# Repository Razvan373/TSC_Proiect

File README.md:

# SmartWatch

Un smartwatch open-source accesibil, construit în jurul microcontrolerului **nRF52840**, cu afișaj **e-paper**, consum redus de energie și conectivitate **Bluetooth Low Energy**.

## Diagramă Bloc

---

## Bill of Materials (BOM)

Tabelul de mai jos conține principalele componente utilizate în proiect, împreună cu capsulele lor, rolul funcțional și link-uri către documentația tehnică unde este disponibilă.

| Componentă | Valoare / Part Number | Pachet | Cant. | Rol | Datasheet |
|-----------|------------------------|--------|-------|-----|-----------|
| NRF52840_QF | nRF52840 | AQFN-73 | 1 | Microcontroler principal cu BLE 5.0 | [Datasheet](https://infocenter.nordicsemi.com/pdf/nRF52840_PS_v1.1.pdf) |
| IC1 | RT6160AWSC | WL-CSP-15 | 1 | Convertor buck-boost DC/DC | [Datasheet](https://www.richtek.com/assets/product_file/RT6160A/DS6160A-05.pdf) |
| IC2 | BMA423 | LGA-12 | 1 | Accelerometru triaxial | [Datasheet](https://www.bosch-sensortec.com/products/motion-sensors/accelerometers/bma423/) |
| IC3 | BQ25180YBGR | DSBGA-8 | 1 | Încărcător pentru baterie LiPo | [Datasheet](https://www.ti.com/lit/ds/symlink/bq25180.pdf) |
| IC4 | DRV2605YZFR | WCSP-9 | 1 | Driver haptic | [Datasheet](https://www.ti.com/lit/ds/symlink/drv2605.pdf) |
| U1 | MAX17048G+T10 | TDFN-8 | 1 | Fuel gauge pentru monitorizarea bateriei | [Datasheet](https://www.analog.com/media/en/technical-documentation/data-sheets/max17048-max17049.pdf) |
| D3 | USBLC6-2SC6Y | SOT-23-6 | 1 | Protecție ESD pentru liniile USB | [Datasheet](https://www.st.com/resource/en/datasheet/usblc6-2.pdf) |
| ANT1 | 2450AT18B100E | SMD | 1 | Antenă chip 2.4GHz | [Datasheet](https://www.johansontechnology.com/datasheets/antennas/2450AT18B100.pdf) |
| X1 | Cristal 32MHz | SMD 2016 | 1 | Sursă principală de ceas | - |
| X2 | Cristal 32.768kHz | SMD 3215 | 1 | Sursă de ceas pentru RTC | - |
| J1 | TC2030-IDC | Tag-Connect | 1 | Interfață SWD pentru programare și debugging | [Datasheet](https://www.tag-connect.com/product/tc2030-idc) |
| J2 | 503480-2400 | FPC-24 | 1 | Conector pentru afișajul e-paper | [Datasheet](https://www.molex.com/en-us/part-list/503480-2400) |
| J4 | KH-TYPE-C-16P | SMD | 1 | Conector USB-C | - |
| Q1 | DMG2305UX-7 | SOT-23 | 1 | MOSFET P-channel pentru circuitul EPD | [Datasheet](https://www.diodes.com/assets/Datasheets/DMG2305UX.pdf) |
| Q3 | SI1308EDL-T1-GE3 | SC-70 | 1 | MOSFET N-channel pentru circuitul EPD | [Datasheet](https://www.vishay.com/docs/68986/si1308edl.pdf) |
| D2, D4, D5 | MBR0530 | SOD-123 | 3 | Diode Schottky pentru etajul EPD | - |
| L1 | 3.9nH | SMD 2012 | 1 | Element din rețeaua RF de adaptare | - |
| L2 | 10µH | SMD 2012 | 1 | Inductor pentru alimentarea nRF | - |
| L3 | 15nH | SMD 2012 | 1 | Filtru RF | - |
| L5 | 68µH | SMD 2012 | 1 | Inductor pentru generatorul EPD | - |
| L7 | FTC252012SR47MBCA | SMD 2012 | 1 | Inductor de putere pentru RT6160 | [JLCPCB](https://jlcpcb.com/partdetail/6763488-FTC252012SR47MBCA/C5832368) |
| SW_UP, SW_DN, SW_ENT | EVP-AKE31A | SMD | 3 | Butoane tactile | - |
| SJ1 | Solder Jumper | SMD | 1 | Jumper de configurare | - |
| R1, R2, R5 | 0Ω | 0201 | 3 | Rezistențe de configurare | - |
| R3, R4 | 3.3kΩ | 0201 | 2 | Pull-up pentru magistrala I2C | - |
| R6, R2_EP_DR, R_PWR_EPD | 10kΩ | 0201 | 3 | Pull-up / pull-down | - |
| R7, R8, R9 | 10kΩ | 0201 | 3 | Pull-down pentru butoane | - |
| R1_USB, R2_USB | 5.1kΩ | 0201 | 2 | Rezistențe CC pentru USB-C | - |
| R_TYPE_SEL | 2.2Ω | 0201 | 1 | Selecție tip display | - |
| R1_EP_DR | 0.47Ω | 0201 | 1 | Limitare / sensing în etajul EPD | - |
| C1, C2, C17, C18 | 12pF | 0201 | 4 | Condensatoare pentru cristale | - |
| C3, C4 | 1pF | 0201 | 2 | Condensatoare pentru adaptare RF | - |
| C9 | 820pF | 0201 | 1 | Condensator de adaptare RF | - |
| C5, C7, C8, C12, C19 | 100nF | 0201 | 5 | Decuplare locală | - |
| C11 | 100pF | 0201 | 1 | Decuplare DEC5 | - |
| C16 | 47nF | 0201 | 1 | Decuplare | - |
| C15 | 1.0µF | 0402 | 1 | Decuplare | - |
| C6, C14, C20, C21, C43, C2-EP-DR | 4.7µF | 0402 | 6 | Condensatoare bulk | - |
| C24, C39, C1-EP-DR | 10µF | 0402 | 3 | Filtrare intrare / ieșire | - |
| C25, C33 | 22µF | 0402 | 2 | Condensatoare ieșire convertor | - |
| C23, C27, C34, C42, EPD_C5 | 0.1µF | 0201 | 5 | Bypass / decuplare | - |
| C29-C32, C37, C38, EPD_C1-C12 | 1µF | 0402 | 15 | Filtrare și stabilizare | - |
| C10, C13, C22 | N.C. | 0201 | 3 | Nepopulate | - |
| Test Pads | - | SMD | 14 | Puncte de test pentru alimentare și debug | - |

---

## Hardware

### Microcontroler principal — nRF52840

Microcontrolerul **nRF52840** reprezintă centrul funcțional al întregului sistem. Acesta asigură procesarea principală, comunicația **Bluetooth Low Energy 5.0**, gestionarea perifericelor și controlul semnalelor digitale necesare funcționării ceasului. Cipul integrează un nucleu **ARM Cortex-M4F** care rulează la **64 MHz**, suficient pentru aplicația vizată, păstrând în același timp un consum redus.

Comunicarea cu restul blocurilor hardware este împărțită astfel:
- **SPI** pentru afișajul e-paper
- **I2C** pentru accelerometru, fuel gauge, încărcător, convertorul DC/DC și driverul haptic
- **GPIO** pentru butoane, semnale de control și linii de întrerupere
- **USB** pentru comunicație și alimentare
- **SWD** pentru programare și depanare

Microcontrolerul este alimentat la **3.3V** din convertorul **RT6160**.

Sursa principală de tact este un cristal de **32 MHz**, conectat la pinii dedicați ai nRF52840. Pentru funcții de timp real și moduri low-power este folosit și un cristal de **32.768 kHz**.

Partea RF este construită în jurul antenei **2450AT18B100E**, conectată la pinul ANT printr-o rețea de adaptare de impedanță formată din **L1, C3, C4 și C9**. Antena a fost poziționată la marginea plăcii, iar în zona de sub aceasta a fost menținut un keepout de cupru pentru a nu afecta performanța radio.

Condensatoarele de decuplare au fost amplasate cât mai aproape de pinii de alimentare, urmând recomandările din designul de referință Nordic.

### Managementul alimentării

#### Încărcător LiPo — BQ25180

Circuitul **BQ25180** se ocupă de încărcarea bateriei LiPo din sursa USB-C. Tensiunea de intrare este preluată de pe linia **VBUS**, iar bateria este conectată pe linia **VBAT**. Acest circuit poate fi configurat prin **I2C**, iar ieșirea sa de întrerupere este conectată la microcontroler pentru semnalizarea evenimentelor de alimentare.

#### Convertor buck-boost — RT6160

Pentru a obține o tensiune stabilă de **3.3V** indiferent de variația tensiunii bateriei, proiectul folosește convertorul **RT6160**. Acesta transformă tensiunea bateriei într-o sursă reglată pentru întreaga logică digitală. Convertorul este conectat la magistrala **I2C**, fiind însoțit de bobina externă și condensatoarele de intrare și ieșire necesare funcționării corecte.

#### Fuel gauge — MAX17048

Circuitul **MAX17048** are rolul de a monitoriza bateria și de a estima starea de încărcare. Acesta comunică prin **I2C**, iar semnalul **ALERT** este dus la un GPIO al microcontrolerului, pentru a permite tratarea rapidă a evenimentelor legate de baterie.

### Afișaj — e-paper 1.54"

Interfața vizuală a ceasului este asigurată de un afișaj **e-paper de 1.54 inch**, cu rezoluție **200 × 200 pixeli**, conectat printr-un conector FPC. Transferul de date se face pe magistrala **SPI**, folosind liniile **MOSI**, **SCK** și **EPD_CS**.

Pe lângă acestea, afișajul mai folosește și semnale GPIO dedicate:
- **EPD_DC**
- **EPD_RST**
- **EPD_BUSY**

Pentru că panoul e-paper are nevoie de tensiuni speciale pentru refresh, a fost introdus un etaj dedicat de generare a tensiunilor, construit cu **Q1**, **Q3**, **D2/D4/D5**, **L5** și mai mulți condensatori. Acest bloc generează liniile **PREVGH** și **PREVGL** necesare funcționării afișajului.

### IMU — BMA423

Pentru detectarea mișcării, proiectul utilizează **BMA423**, un accelerometru triaxial cu consum redus. Acesta este conectat la microcontroler prin **I2C** și oferă două ieșiri de întrerupere, **IMU_INT1** și **IMU_INT2**, utilizabile pentru funcții precum detectarea mișcării, a pașilor sau trezirea sistemului.

### Driver haptic — DRV2605

Feedback-ul tactil este realizat prin circuitul **DRV2605**, care comandă motorul de vibrație. Acesta comunică prin **I2C** și este activat prin semnalul **HAPTIC_EN** controlat de microcontroler.

### USB-C și protecție ESD

Conectorul **USB-C** este folosit atât pentru alimentare, cât și pentru comunicație USB. Liniile de date sunt protejate cu circuitul **USBLC6**, iar pinii **CC** sunt configurați prin rezistențe de **5.1kΩ**, astfel încât portul să fie recunoscut corect în modul device.

### Interfață de debugging — SWD

Programarea și depanarea sunt realizate printr-un conector **Tag-Connect TC2030**, care expune semnalele:
- **SWDIO**
- **SWDCLK**
- **SWO**
- **RESET**
- **3.3V**
- **GND**

Această soluție elimină necesitatea unui header permanent și ajută la păstrarea unui format compact al plăcii.

---

## Mapare pini nRF52840

Tabelul următor prezintă rolul principal al pinilor utilizați pe microcontrolerul nRF52840 în cadrul proiectului.

| Pin | Semnal | Funcție | Interfață |
|-----|--------|---------|-----------|
| P0.00 / XL1 | XL1 | Intrare cristal 32.768kHz | Clock |
| P0.01 / XL2 | XL2 | Ieșire cristal 32.768kHz | Clock |
| P0.04 / AIN2 | IMU_INT1 | Întrerupere 1 de la accelerometru | GPIO |
| P0.05 / AIN3 | IMU_INT2 | Întrerupere 2 de la accelerometru | GPIO |
| P0.06 | EPD_CS | Chip Select pentru e-paper | SPI |
| P0.07 | EPD_DC | Selectare date / comandă display | GPIO |
| P0.08 | EPD_RST | Reset pentru display | GPIO |
| P0.09 / NFC1 | PMIC_INT | Întrerupere de la BQ25180 | GPIO |
| P0.11 | SCK | Clock SPI pentru e-paper | SPI |
| P0.12 | MOSI | Linie date SPI pentru e-paper | SPI |
| P0.13 | EPD_BUSY | Semnal busy de la display | GPIO |
| P0.14 | SCL | Clock magistrală I2C | I2C |
| P0.15 | SDA | Linie date magistrală I2C | I2C |
| P0.18 / RESET | RESET | Reset sistem | Reset |
| P0.19 | HAPTIC_EN | Enable pentru driverul haptic | GPIO |
| P0.26 | SW_UP | Buton sus | GPIO |
| P0.27 | SW_DN | Buton jos | GPIO |
| P1.00 | SW_ENT | Buton enter / select | GPIO |
| P1.01 | ALERT | Alertă de la MAX17048 | GPIO |
| P1.09 | SWO | Debug trace output | Debug |
| XC1 / XC2 | Crystal | Cristal 32MHz | Clock |
| ANT | RF | Antenă prin rețea de adaptare | RF |
| VBUS | USB_VBUS | Alimentare USB 5V | Power |
| D+ / D- | USB Data | Linii de date USB | USB |
| SWDIO | Debug | Linie date SWD | Debug |
| SWDCLK | Debug | Linie clock SWD | Debug |

**Magistrala I2C** este comună pentru:
- **BMA423**
- **BQ25180**
- **RT6160**
- **DRV2605**
- **MAX17048**

Liniile **SDA** și **SCL** sunt trase la **3.3V** prin rezistențele **R3** și **R4**.

---

## Detalii design PCB

### Specificații generale

- **Dimensiuni placă:** 46 mm × 35 mm
- **Formă:** colțuri rotunjite
- **Număr de straturi:** 2
- **Straturi folosite:** Top și Bottom
- **Grosime PCB:** 1.0 mm
- **Lățime trasee semnal:** 0.15 mm
- **Lățime trasee putere:** 0.3 mm
- **Montaj componente:** exclusiv pe stratul Top

### Organizarea straturilor

Placa a fost proiectată pe **două straturi**, iar ambele straturi includ și **zone de plan de masă (GND pour)** pentru a îmbunătăți returul de curent, stabilitatea electrică și comportamentul EMI.

| Strat | Rol principal |
|-------|---------------|
| Top | rutare semnale, plasare componente, plan GND |
| Bottom | rutare suplimentară și plan GND |

### Decizii de proiectare și erori acceptate

În timpul proiectării au existat anumite avertismente DRC care au fost analizate manual și acceptate, deoarece rezultau din constrângeri reale de spațiu sau din cerințe mecanice.

#### Erori de lățime traseu

Pentru liniile de putere precum **3V3**, **VBAT**, **VBUS** sau alte rețele similare, regula de proiectare impunea o lățime de **0.3 mm**. În anumite zone foarte aglomerate ale plăcii, mai ales în apropierea capsulelor fine și a grupurilor dense de componente pasive, această lățime nu a putut fi păstrată pe întreaga lungime, astfel că unele segmente scurte au fost rutate mai îngust. Aceste cazuri au fost acceptate.

#### Erori de clearance

În unele regiuni compacte, în special în jurul microcontrolerului și în zonele cu densitate mare de trasee, anumite segmente de cupru au ajuns mai aproape decât clearance-ul ideal. Aceste situații au fost verificate manual și nu au indicat existența unor scurtcircuite reale.

#### Avertismente legate de planele GND

Fiindcă atât pe Top, cât și pe Bottom au fost folosite planuri de masă, anumite mesaje de clearance sau suprapunere au apărut între zone care aparțin aceleiași rețele **GND**. Aceste avertismente nu afectează funcționarea electrică a plăcii.

#### Extindere peste conturul plăcii

Butoanele tactile și conectorul USB-C sunt poziționate astfel încât să iasă parțial în afara conturului PCB-ului. Acest lucru a fost făcut intenționat pentru alinierea cu decupajele carcasei.

#### Componente nepopulate

Anumite condensatoare marcate **N.C.** sau **DNP** au rămas în schemă și layout pentru compatibilitate cu designul de referință, dar nu sunt montate în varianta finală.

#### Vias de masă și continuitate GND

Au fost adăugate mai multe căi de masă distribuite pe placă pentru a îmbunătăți continuitatea între planele GND și pentru a oferi trasee de retur mai bune, mai ales în jurul zonei RF și a microcontrolerului.

---

## Design PCB

Layout-ul plăcii a fost realizat cu accent pe compactitate, integrare mecanică și păstrarea unor rute cât mai clare între blocurile funcționale. Toate componentele au fost montate pe stratul **Top**, ceea ce simplifică asamblarea și reduce complexitatea mecanică.

Microcontrolerul a fost poziționat central pentru a facilita distribuția semnalelor către afișaj, senzori, partea de alimentare și interfața de debugging. Blocurile de alimentare au fost păstrate relativ aproape unele de altele pentru a minimiza lungimea traseelor de putere, iar zona RF a fost plasată la marginea plăcii pentru a permite funcționarea corectă a antenei.

În realizarea layout-ului au fost urmărite următoarele principii:
- trasee scurte pentru alimentare și decuplare
- gruparea componentelor pe funcții
- separarea cât mai clară a zonei RF de restul circuitului
- acces mecanic bun pentru USB-C și butoane
- folosirea planurilor GND pe ambele straturi pentru integritate electrică mai bună

Imaginile cu stratul superior și cel inferior sunt incluse în secțiunea de imagini a repository-ului pentru a evidenția modul de rutare și distribuția componentelor.
| Top Layer | Bottom Layer |
|:---:|:---:|
|  |  |

---

## Design schematic

Schema electrică a fost organizată modular, astfel încât fiecare subsistem important să poată fi urmărit separat și ușor de înțeles. Proiectul include blocuri distincte pentru:
- microcontroler și tact
- alimentare și încărcare baterie
- monitorizare baterie
- afișaj e-paper și etajul său de comandă
- accelerometru
- driver haptic
- interfață USB
- interfață SWD

Această structurare ajută atât în faza de proiectare, cât și în etapa de verificare și review. Conexiunile dintre blocuri sunt realizate coerent, iar magistralele principale, cum ar fi **I2C** și **SPI**, sunt evidențiate clar în schemă.

De asemenea, schema conține și componente auxiliare importante:
- rezistențe de pull-up și pull-down
- condensatoare de decuplare și filtrare
- elemente de adaptare RF
- conectori și puncte de test

Capturile de ecran ale schemei sunt incluse în repository pentru a susține documentația hardware.

---

## Structura repository-ului

Structura proiectului este organizată astfel încât fișierele de proiectare, fabricație, randare și documentare să fie ușor de identificat.

```text
├── Hardware/
│   ├── InkTime_Schematic.sch
│   └── InkTime_Board.brd
├── Manufacturing/
│   ├── gerbers.zip
│   ├── InkTime_BOM.bom
│   └── InkTime_PnP.cpl
├── Mechanical/
│   ├── InkTime_step.step
│   └── InkTime_complete.f3z
├── Images/
│   ├── 2D_PCB/
│   ├── 3D_PCB/
│   ├── InkTime/
│   └── Schematic/
├── LICENSE
└── README.md

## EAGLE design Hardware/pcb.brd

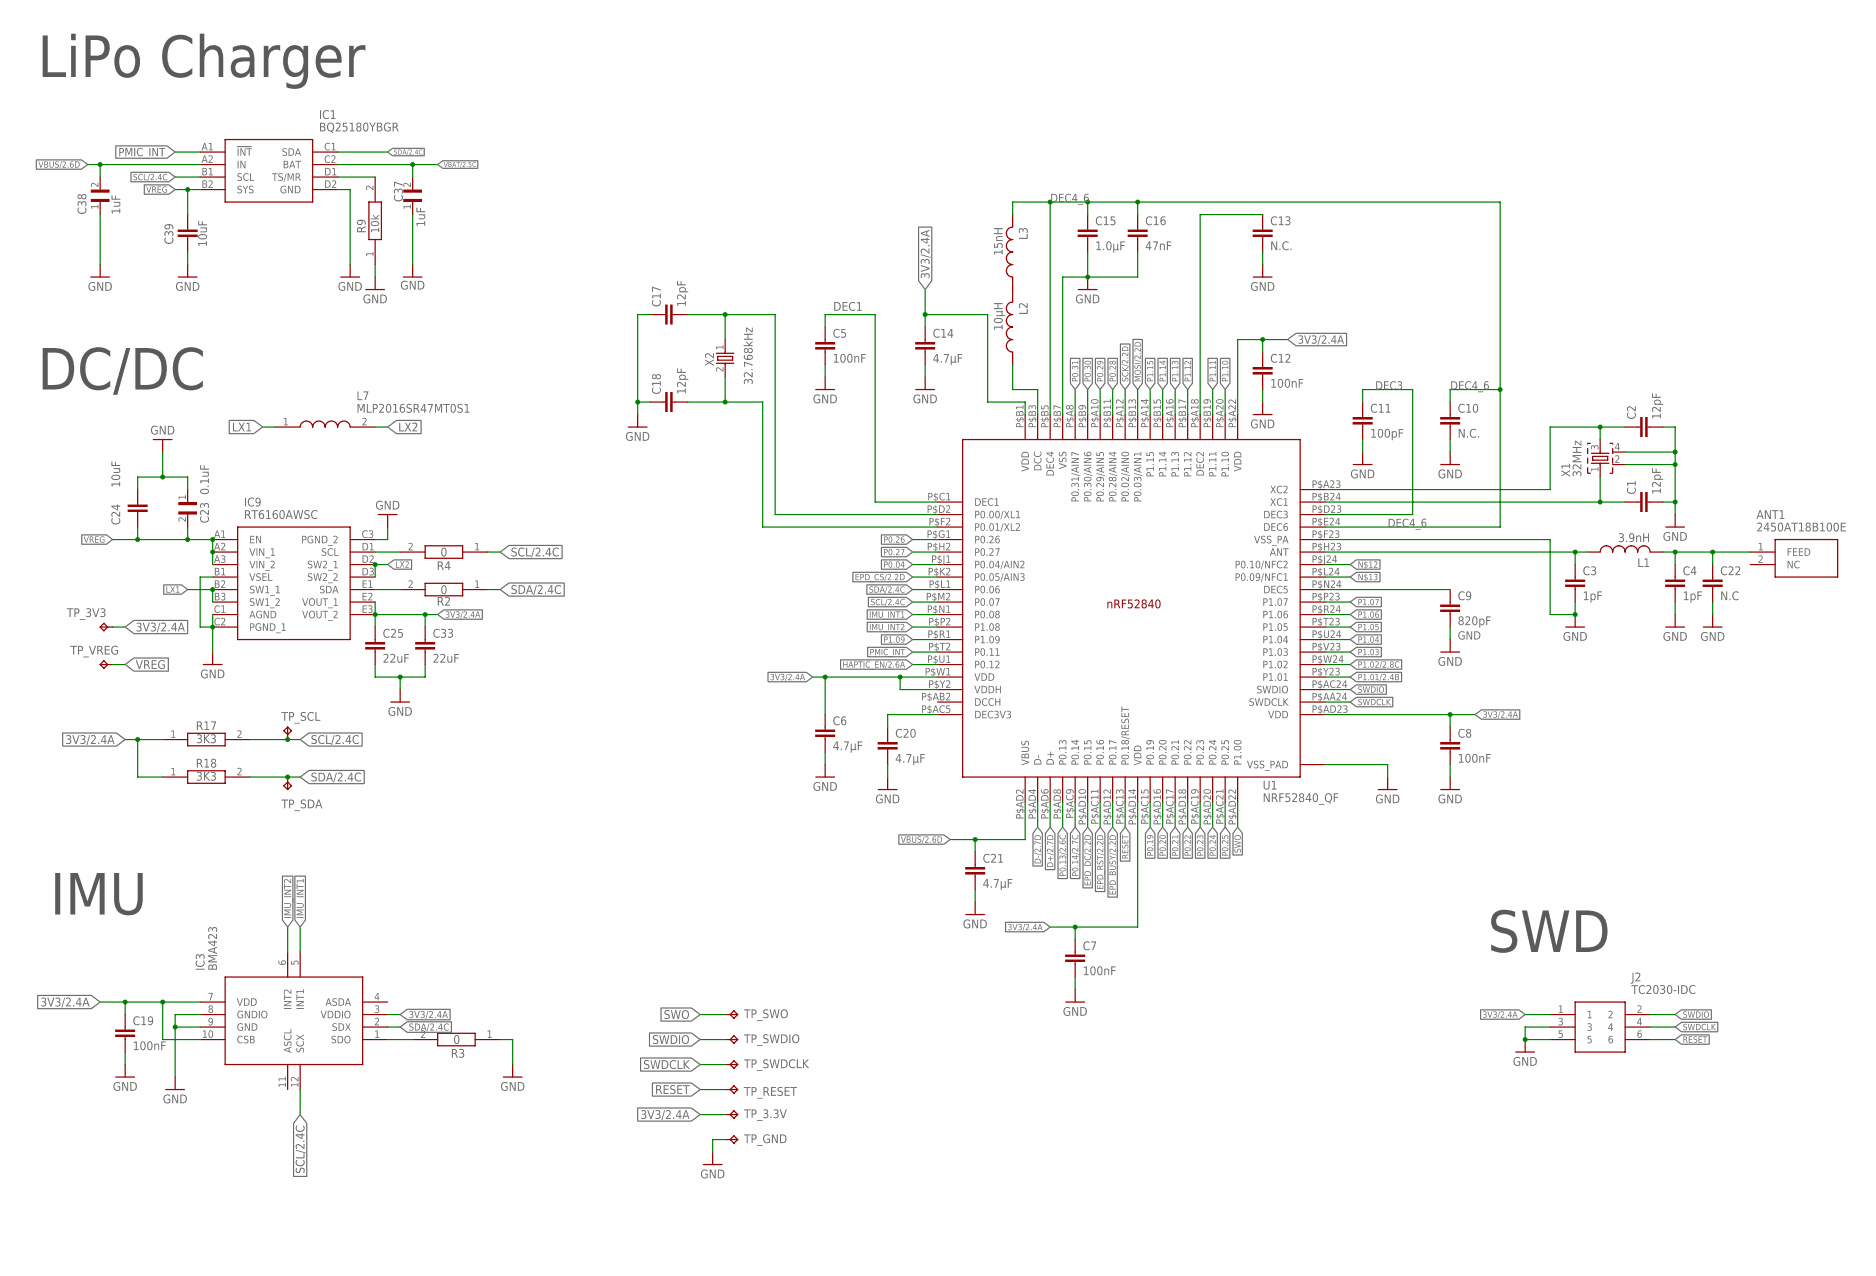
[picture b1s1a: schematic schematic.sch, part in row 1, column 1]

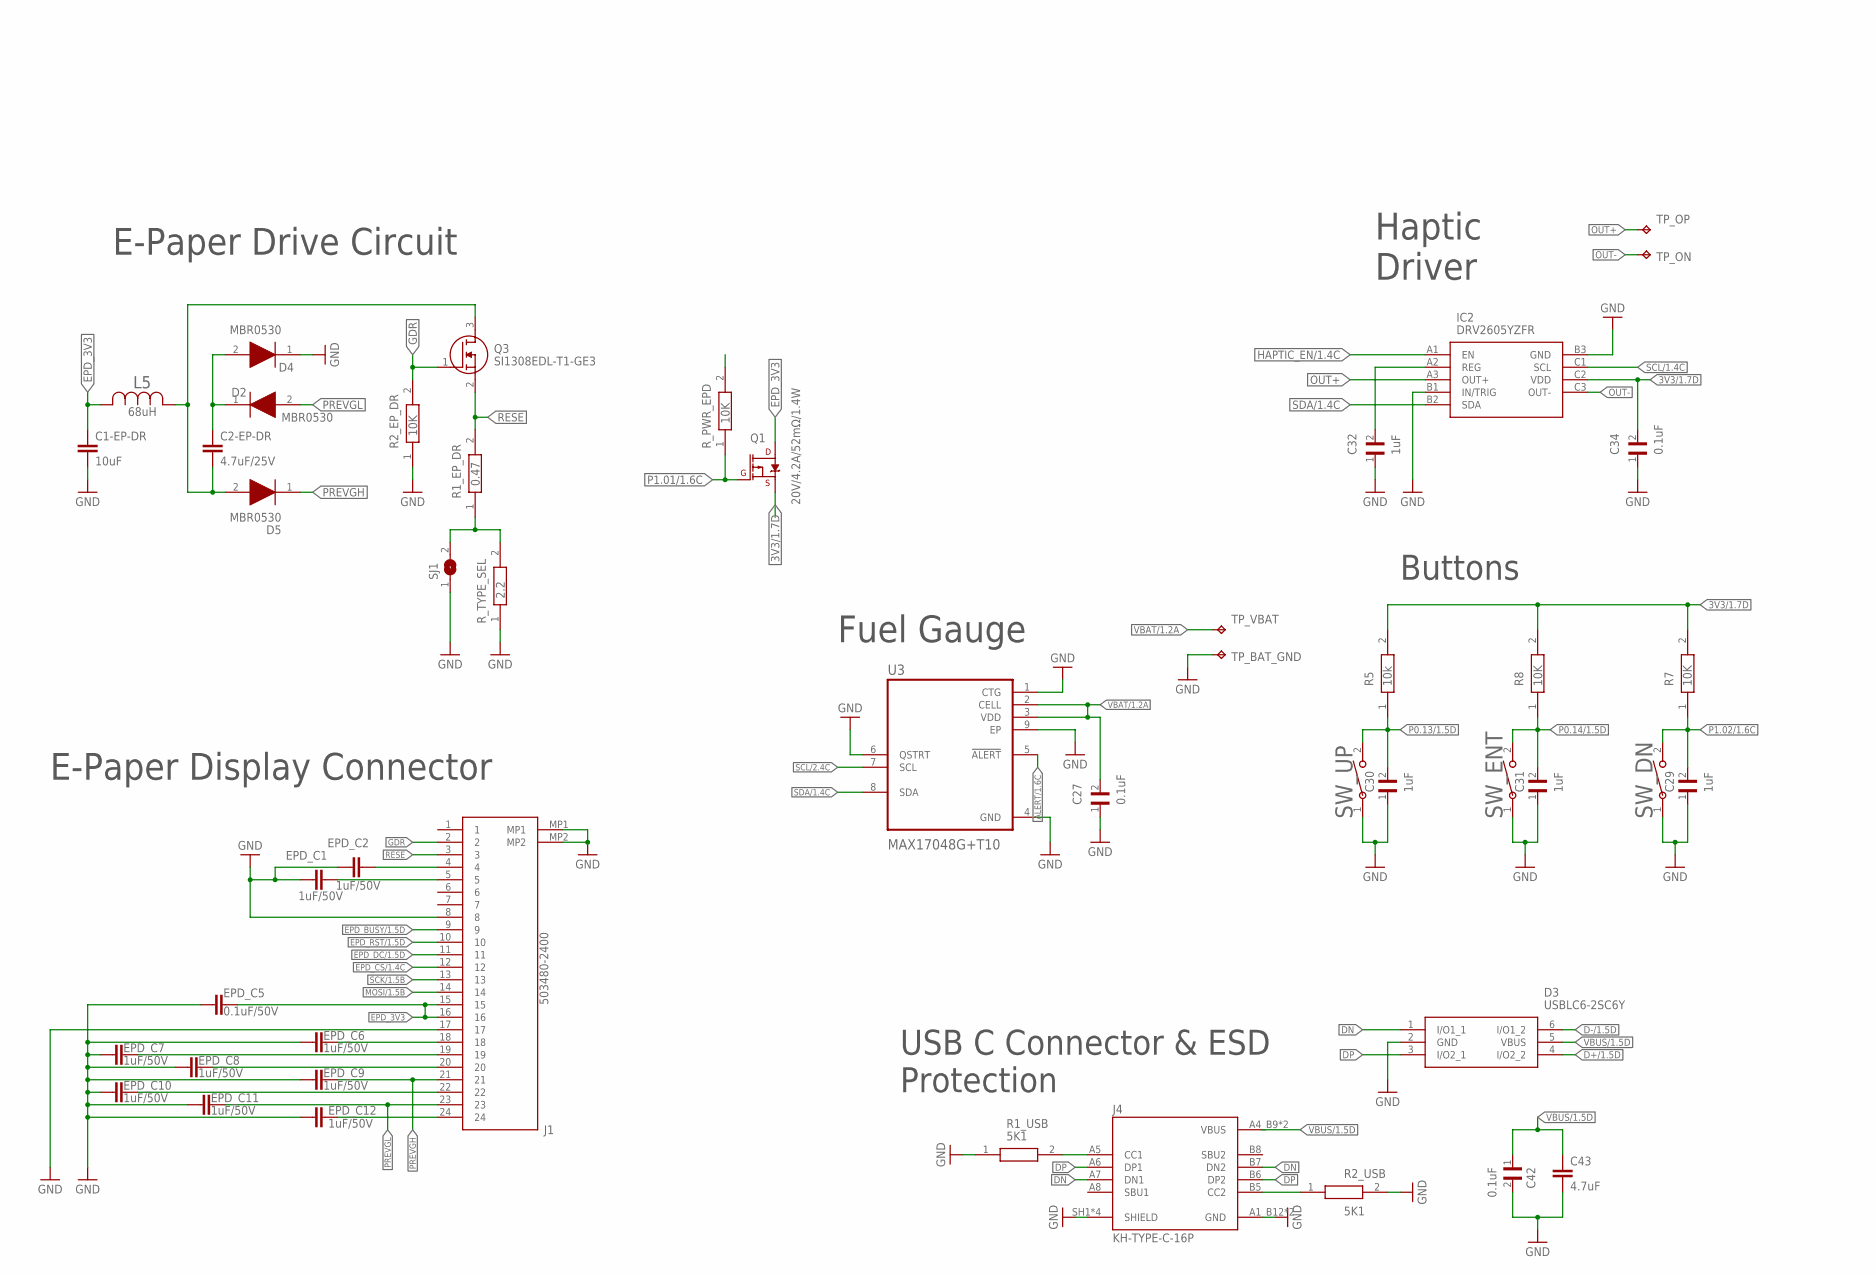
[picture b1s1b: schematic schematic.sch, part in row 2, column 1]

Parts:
ANT1: 2450AT18B100E; 2450AT18B100E_ANTC3216X140N
C1, C2, C17, C18: 12pF; NORDIC_NRF_3_RESC0201_L
C1-EP-DR, C24, C39: 10uF; PERFECT_0402_0402
C2-EP-DR: 4.7uF/25V; PERFECT_0402_0402
C3, C4: 1pF; NORDIC_NRF_3_RESC0201_L
C5, C7, C8, C12, C19: 100nF; NORDIC_NRF_3_RESC0201_L
C6, C14, C20, C21: 4.7µF; PERFECT_0402_0402
C9: 820pF; NORDIC_NRF_3_RESC0201_L
C10, C13: N.C.; NORDIC_NRF_3_RESC0201_L
C11: 100pF; NORDIC_NRF_3_RESC0201_L
C15: 1.0µF; PERFECT_0402_0402
C16: 47nF; NORDIC_NRF_3_RESC0201_L
C22: N.C; NORDIC_NRF_3_RESC0201_L
C23, C27, C34, C42: 0.1uF; ERA-1AEB3401C_0201
C25, C33: 22uF; PERFECT_0402_0402
C29, C30, C31, C32, C37, C38: 1uF; ERA-1AEB3401C_0201
C43: 4.7uF; PERFECT_0402_0402
D2, D4, D5: MBR0530; ESP32_C6_LIBRARY_5_SOD3716X135N
D3: USBLC6-2SC6Y; ESP32_C6_LIBRARY_3_SOT95P280X145-6N
EPD_C1, EPD_C2, EPD_C6, EPD_C7, EPD_C8, EPD_C9, EPD_C10, EPD_C11, EPD_C12: 1uF/50V; PERFECT_0402_0402
EPD_C5: 0.1uF/50V; NORDIC_NRF_3_RESC0201_L
IC1: BQ25180YBGR; BQ25180YBGR_BGA8C40P2X4_100X155X50
IC2: DRV2605YZFR; DRV2605YZFR_BGA9C50P3X3_144X144X62
IC3: BMA423; BMA423_BMA423
IC9: RT6160AWSC; RT6160AWSC_BGA15C40P3X5_140X230X60
J1: 503480-2400; 503480-2400_5034802400
J2: TC2030-IDC; TC2030-IDC_TC2030IDC
J4: KH-TYPE-C-16P; KH-TYPE-C-16P_KINGHELM_KH-TYPE-C-16P
L1: 3.9nH; NORDIC_NRF_2_RESC0402_N
L2: 10µH; NORDIC_NRF_2_RESC0402_N
L3: 15nH; NORDIC_NRF_2_RESC0402_N
L5: 68uH; ESP32_C6_LIBRARY_2_IND_4828-WE-TPC_WRE
L7: MLP2016SR47MT0S1; MLP2016SR47MT0S1_INDC2016X100N
Q1: 20V/4.2A/52mΩ/1.4W; ESP32_C6_LIBRARY_4_ESP32_C6_LIBRARY_4_ESP32_C6_LIBRARY_4_ES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
Q3: SI1308EDL-T1-GE3; ESP32_C6_LIBRARY_6_SOT65P210X110-3N
R1_EP_DR: 0.47; CPF0201D7K68C1_0201
R1_USB, R2_USB: 5K1; CPF0201D7K68C1_0201
R2, R4: 0; ERA-1AEB3401C_0201
R2_EP_DR, R7, R8: 10K; CPF0201D7K68C1_0201
R3: 0; CPF0201D7K68C1_0201
R5: 10k; CPF0201D7K68C1_0201
R9: 10k; ERA-1AEB3401C_0201
R17, R18: 3K3; ERA-1AEB3401C_0201
R_PWR_EPD: 10K; CPF0201D7K68C1_0201
R_TYPE_SEL: 2.2; CPF0201D7K68C1_0201
SJ1: ESP32_C6_LIBRARY_7_JUMPER_SJ
SW_DN: 2025-10-22_07-23-44_LIBRARY_EVP-AKE31ASW_EVP-AKE3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; 2025-10-22_07-23-44_LIBRARY_SW_EVP-AKE31A_PAN
SW_ENT: 2025-10-22_07-23-44_LIBRARY_EVP-AKE31ASW_EVP-AKE3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; 2025-10-22_07-23-44_LIBRARY_SW_EVP-AKE31A_PAN
SW_UP: 2025-10-22_07-23-44_LIBRARY_EVP-AKE31ASW_EVP-AKE3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; 2025-10-22_07-23-44_LIBRARY_SW_EVP-AKE31A_PAN
TP_3.3V, TP_3V3: HECTOR_WATCH_1_TPTP20R; HECTOR_WATCH_1_TP20R
TP_BAT_GND: HECTOR_WATCH_1_TPTP20R; HECTOR_WATCH_1_TP20R
TP_GND: HECTOR_WATCH_1_TPTP20R; HECTOR_WATCH_1_TP20R
TP_ON: HECTOR_WATCH_1_TPTP20R; HECTOR_WATCH_1_TP20R
TP_OP: HECTOR_WATCH_1_TPTP20R; HECTOR_WATCH_1_TP20R
TP_RESET: HECTOR_WATCH_1_TPTP20R; HECTOR_WATCH_1_TP20R
TP_SCL: HECTOR_WATCH_1_TPTP20R; HECTOR_WATCH_1_TP20R
TP_SDA: HECTOR_WATCH_1_TPTP20R; HECTOR_WATCH_1_TP20R
TP_SWDCLK: HECTOR_WATCH_1_TPTP20R; HECTOR_WATCH_1_TP20R
TP_SWDIO: HECTOR_WATCH_1_TPTP20R; HECTOR_WATCH_1_TP20R
TP_SWO: HECTOR_WATCH_1_TPTP20R; HECTOR_WATCH_1_TP20R
TP_VBAT: HECTOR_WATCH_1_TPTP20R; HECTOR_WATCH_1_TP20R
TP_VREG: HECTOR_WATCH_1_TPTP20R; HECTOR_WATCH_1_TP20R
U1: NRF52840_QF; NORDIC_NRF_4_AQFN50P700X700X85_HS-74N
U3: MAX17048G+T10; ESP32_C6_LIBRARY_SON50P200X200X80-9N
X1: 32MHz; NORDIC_NRF_BT-XTAL_2016_N
X2: 32.768kHz; NORDIC_NRF_1_XTAL_3215_N

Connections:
3V3/1.7D: C34.2, IC2.C2 (VDD), Q1.2 (S), R5.2, R7.2, R8.2
3V3/2.4A: C6.1, C7.1, C8.1, C12.1, C14.1, C19.1, C25.1, C33.1, IC3.3 (VDDIO), IC3.7 (VDD), IC3.10 (CSB), IC9.E2 (VOUT_1), IC9.E3 (VOUT_2), J2.1, R17.1, R18.1, TP_3.3V.TP, TP_3V3.TP, U1.P$A22 (VDD), U1.P$AD14 (VDD), U1.P$AD23 (VDD), U1.P$B1 (VDD), U1.P$W1 (VDD), U1.P$Y2 (VDDH)
ALERT/1.6C: U3.5 (!ALERT)
D+/1.5D: D3.4 (I/O2_2)
D+/2.7D: U1.P$AD6 (D+)
D-/1.5D: D3.6 (I/O1_2)
D-/2.7D: U1.P$AD4 (D-)
DEC1: C5.1, U1.P$C1 (DEC1)
DEC3: C11.1, U1.P$D23 (DEC3)
DEC4_6: C10.1, C15.1, C16.1, L3.2, U1.P$B5 (DEC4), U1.P$E24 (DEC6)
DN: D3.1 (I/O1_1), J4.A7 (DN1), J4.B7 (DN2)
DP: D3.3 (I/O2_1), J4.A6 (DP1), J4.B6 (DP2)
EPD_3V3: C1-EP-DR.1, EPD_C5.2, J1.15, J1.16, L5.2, Q1.3 (D)
EPD_BUSY/1.5D: J1.9
EPD_BUSY/2.2D: U1.P$AD12 (P0.17)
EPD_CS/1.4C: J1.12
EPD_CS/2.2D: U1.P$K2 (P0.05/AIN3)
EPD_DC/1.5D: J1.11
EPD_DC/2.2D: U1.P$AD10 (P0.15)
EPD_RST/1.5D: J1.10
EPD_RST/2.2D: U1.P$AC11 (P0.16)
GDR: J1.2, Q3.1 (G), R2_EP_DR.2
GND: C1.2, C1-EP-DR.2, C2.2, C3.2, C4.2, C5.2, C6.2, C7.2, C8.2, C9.2, C10.2, C11.2, C12.2, C13.2, C14.2, C15.2, C16.2, C17.1, C18.1, C19.2, C20.2, C21.2, C22.2, C23.1, C24.1, C25.2, C27.1, C29.1, C30.1, C31.1, C32.1, C33.2, C34.1, C37.1, C38.1, C39.2, C42.2, C43.2, D3.2 (GND), D4.1 (K), EPD_C1.1, EPD_C2.1, EPD_C5.1, EPD_C6.1, EPD_C7.1, EPD_C8.1, EPD_C9.1, EPD_C10.1, EPD_C11.1, EPD_C12.1, IC1.D2 (GND), IC2.B1 (IN/TRIG), IC2.B3 (GND), IC3.8 (GNDIO), IC3.9 (GND), IC9.B1 (VSEL), IC9.C1 (AGND), IC9.C2 (PGND_1), IC9.C3 (PGND_2), J1.8, J1.17, J1.MP1, J1.MP2, J2.3, J2.5, J4.A1_B12 (GND), J4.A12_B1 (GND), J4.SH1 (SHIELD), J4.SH2 (SHIELD), J4.SH3 (SHIELD), J4.SH4 (SHIELD), R1_USB.1, R2_EP_DR.1, R2_USB.2, R3.1, R9.1, R_TYPE_SEL.1, SJ1.1, SW_DN.1, SW_ENT.1, SW_UP.1, TP_BAT_GND.TP, TP_GND.TP, U1.P$74 (VSS_PAD), U1.P$75 (VSS_PAD), U1.P$76 (VSS_PAD), U1.P$77 (VSS_PAD), U1.P$78 (VSS_PAD), U1.P$79 (VSS_PAD), U1.P$80 (VSS_PAD), U1.P$81 (VSS_PAD), U1.P$82 (VSS_PAD), U1.P$83 (VSS_PAD), U1.P$84 (VSS_PAD), U1.P$85 (VSS_PAD), U1.P$86 (VSS_PAD), U1.P$87 (VSS_PAD), U1.P$88 (VSS_PAD), U1.P$89 (VSS_PAD), U1.P$90 (VSS_PAD), U1.P$B7 (VSS), U1.P$F23 (VSS_PA), U3.1 (CTG), U3.4 (GND), U3.6 (QSTRT), U3.9 (EP), X1.2, X1.4
HAPTIC_EN/1.4C: IC2.A1 (EN)
HAPTIC_EN/2.6A: U1.P$U1 (P0.12)
IMU_INT1: IC3.5 (INT1), U1.P$N1 (P0.08)
IMU_INT2: IC3.6 (INT2), U1.P$P2 (P1.08)
LX1: IC9.B2 (SW1_1), IC9.B3 (SW1_2), L7.1
LX2: IC9.D2 (SW2_1), IC9.D3 (SW2_2), L7.2
MOSI/1.5B: J1.14
MOSI/2.2D: U1.P$B13 (P0.03/AIN1)
unnamed: IC9.D1 (SCL), R4.2
unnamed: IC1.D1 (TS/MR), R9.2
unnamed: IC9.E1 (SDA), R2.2
unnamed: C18.2, U1.P$F2 (P0.01/XL2), X2.2
unnamed: C17.2, U1.P$D2 (P0.00/XL1), X2.1
unnamed: C2.1, U1.P$A23 (XC2), X1.3
unnamed: C1.1, U1.P$B24 (XC1), X1.1
unnamed: L2.2, L3.1
unnamed: C2-EP-DR.1, D2.1 (K), D4.2 (A)
unnamed: C2-EP-DR.2, D5.2 (A), L5.1, Q3.3 (D)
unnamed: C3.1, L1.1, U1.P$H23 (ANT)
unnamed: C9.1, U1.P$N24 (DEC5)
unnamed: EPD_C2.2, J1.4
unnamed: ANT1.1 (FEED), C4.1, C22.1, L1.2
unnamed: C13.1, U1.P$A18 (DEC2)
unnamed: EPD_C1.2, J1.5
unnamed: C32.2, IC2.A2 (REG)
unnamed: C20.1, U1.P$AC5 (DEC3V3)
unnamed: J4.A5 (CC1), R1_USB.2
unnamed: R1_EP_DR.1, R_TYPE_SEL.2, SJ1.2
unnamed: J4.B5 (CC2), R2_USB.1
unnamed: EPD_C6.2, J1.18
unnamed: L2.1, U1.P$B3 (DCC)
unnamed: EPD_C7.2, J1.19
unnamed: EPD_C8.2, J1.20
unnamed: EPD_C10.2, J1.22
unnamed: EPD_C12.2, J1.24
OUT+: IC2.A3 (OUT+), TP_OP.TP
OUT-: IC2.C3 (OUT-), TP_ON.TP
P0.04: U1.P$J1 (P0.04/AIN2)
P0.13/1.5D: C30.2, R5.1, SW_UP.2
P0.13/2.6C: U1.P$AD8 (P0.13)
P0.14/1.5D: C31.2, R8.1, SW_ENT.2
P0.14/2.7C: U1.P$AC9 (P0.14)
P0.19: U1.P$AC15 (P0.19)
P0.20: U1.P$AD16 (P0.20)
P0.21: U1.P$AC17 (P0.21)
P0.22: U1.P$AD18 (P0.22)
P0.23: U1.P$AC19 (P0.23)
P0.24: U1.P$AD20 (P0.24)
P0.25: U1.P$AC21 (P0.25)
P0.26: U1.P$G1 (P0.26)
P0.27: U1.P$H2 (P0.27)
P0.28: U1.P$B11 (P0.28/AIN4)
P0.29: U1.P$A10 (P0.29/AIN5)
P0.30: U1.P$B9 (P0.30/AIN6)
P0.31: U1.P$A8 (P0.31/AIN7)
P1.01/1.6C: Q1.1 (G), R_PWR_EPD.1
P1.01/2.4B: U1.P$Y23 (P1.01)
P1.02/1.6C: C29.2, R7.1, SW_DN.2
P1.02/2.8C: U1.P$W24 (P1.02)
P1.03: U1.P$V23 (P1.03)
P1.04: U1.P$U24 (P1.04)
P1.05: U1.P$T23 (P1.05)
P1.06: U1.P$R24 (P1.06)
P1.07: U1.P$P23 (P1.07)
P1.09: U1.P$R1 (P1.09)
P1.10: U1.P$A20 (P1.10)
P1.11: U1.P$B19 (P1.11)
P1.12: U1.P$B17 (P1.12)
P1.13: U1.P$A16 (P1.13)
P1.14: U1.P$B15 (P1.14)
P1.15: U1.P$A14 (P1.15)
PMIC_INT: IC1.A1 (!INT), U1.P$T2 (P0.11)
PREVGH: D5.1 (K), EPD_C9.2, J1.21
PREVGL: D2.2 (A), EPD_C11.2, J1.23
RESE: J1.3, Q3.2 (S), R1_EP_DR.2
RESET: J2.6, TP_RESET.TP, U1.P$AC13 (P0.18/RESET)
SCK/1.5B: J1.13
SCK/2.2D: U1.P$A12 (P0.02/AIN0)
SCL/1.4C: IC2.C1 (SCL)
SCL/2.4C: IC1.B1 (SCL), IC3.12 (SCX), R4.1, R17.2, TP_SCL.TP, U1.P$M2 (P0.07), U3.7 (SCL)
SCL/2.4C1: IC3.1 (SDO), R3.2
SDA/1.4C: IC2.B2 (SDA), U3.8 (SDA)
SDA/2.4C: IC1.C1 (SDA), IC3.2 (SDX), R2.1, R18.2, TP_SDA.TP, U1.P$L1 (P0.06)
SWDCLK: J2.4, TP_SWDCLK.TP, U1.P$AA24 (SWDCLK)
SWDIO: J2.2, TP_SWDIO.TP, U1.P$AC24 (SWDIO)
SWO: TP_SWO.TP, U1.P$AD22 (P1.00)
VBAT/1.2A: C27.2, TP_VBAT.TP, U3.2 (CELL), U3.3 (VDD)
VBAT/2.5C: C37.2, IC1.C2 (BAT)
VBUS/1.5D: C42.1, C43.1, D3.5 (VBUS), J4.A4_B9 (VBUS), J4.A9_B4 (VBUS)
VBUS/2.6D: C21.1, C38.2, IC1.A2 (IN), U1.P$AD2 (VBUS)
VREG: C23.2, C24.2, C39.1, IC1.B2 (SYS), IC9.A1 (EN), IC9.A2 (VIN_1), IC9.A3 (VIN_2), TP_VREG.TP

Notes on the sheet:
IMU
DC/DC
LiPo Charger
SWD
Haptic Driver
E-Paper Drive Circuit
Fuel Gauge
E-Paper Display Connector
USB C Connector & ESD Protection
Buttons

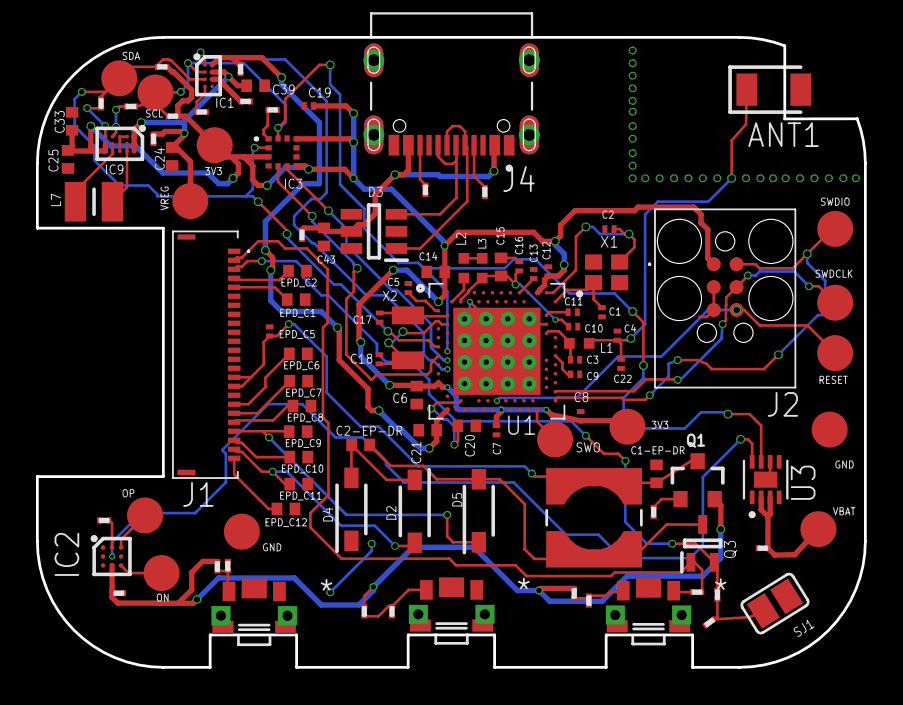
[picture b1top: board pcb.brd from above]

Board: 2 copper layers, 46.0 x 35.0 mm, 105 parts (0 on the bottom side), 64 nets.

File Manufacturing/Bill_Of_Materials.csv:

Reference Designators;Quantity;Description;Package;Value;Manufacturer;Manufacturer Part Number;Vendor;Vendor Part Number;Top/Bottom;
;1;PCB Board;Board;;;;;;;
ANT1;1;Antennas 2.45GHz ANTENNA;2450AT18B100E_ANTC3216X140N;2450AT18B100E;;;;;Top;
C1, C2, C17, C18;4;Generic chip capacitor;NORDIC_NRF_3_RESC0201_L;12pF;;;;;Top;
C1-EP-DR, C24, C39;3;0402 (1005 Metric);PERFECT_0402_0402;10uF;;;;;Top;
C2-EP-DR;1;0402 (1005 Metric);PERFECT_0402_0402;4.7uF/25V;;;;;Top;
C3, C4;2;Generic chip capacitor;NORDIC_NRF_3_RESC0201_L;1pF;;;;;Top;
C5, C7, C8, C12, C19;5;Generic chip capacitor;NORDIC_NRF_3_RESC0201_L;100nF;;;;;Top;
C6, C14, C20, C21;4;0402 (1005 Metric);PERFECT_0402_0402;4.7µF;;;;;Top;
C9;1;Generic chip capacitor;NORDIC_NRF_3_RESC0201_L;820pF;;;;;Top;
C10, C13;2;Generic chip capacitor;NORDIC_NRF_3_RESC0201_L;N.C.;;;;;Top;
C11;1;Generic chip capacitor;NORDIC_NRF_3_RESC0201_L;100pF;;;;;Top;
C15;1;0402 (1005 Metric);PERFECT_0402_0402;1.0µF;;;;;Top;
C16;1;Generic chip capacitor;NORDIC_NRF_3_RESC0201_L;47nF;;;;;Top;
C22;1;Generic chip capacitor;NORDIC_NRF_3_RESC0201_L;N.C;;;;;Top;
C23, C27, C34, C42;4;Check availability;GRM011R60J152KE01L_1_0201;0.1uF;;;;;Top;
C25, C33;2;0402 (1005 Metric);PERFECT_0402_0402;22uF;;;;;Top;
C29, C30, C31, C32, C37, C38;6;Check availability;GRM011R60J152KE01L_1_0201;1uF;;;;;Top;
C43;1;0402 (1005 Metric);PERFECT_0402_0402;4.7uF;;;;;Top;
D2, D4, D5;3;ON SEMICONDUCTOR - MBR0530 - DIODE, SCHOTTKY, 0.5A, 30V, SOD-123;SOD3716X135N;MBR0530;;;;;Top;
D3;1;Low Cap. ESD Protection Auto SOT-23-6 STMicroelectronics USBLC6-2SC6Y, Dual Uni-Directional TVS Diode Array, 6-Pin SOT-23;SOT95P280X145-6N;USBLC6-2SC6Y;;;;;Top;
EPD_C1, EPD_C2, EPD_C6, EPD_C7, EPD_C8, EPD_C9, EPD_C10, EPD_C11, EPD_C12;9;0402 (1005 Metric);PERFECT_0402_0402;1uF/50V;;;;;Top;
EPD_C5;1;Generic chip capacitor;NORDIC_NRF_3_RESC0201_L;0.1uF/50V;;;;;Top;
IC1;1;Charger IC Lithium Ion/Polymer, Lithium Iron Phosphate 8-DSBGA (1.6x1.1);BQ25180YBGR_BGA8C40P2X4_100X155X50;BQ25180YBGR;;;;;Top;
IC2;1;Haptic Driver for ERM/LRA with Built-In Library and Smart Loop Architecture;DRV2605YZFR_BGA9C50P3X3_144X144X62;DRV2605YZFR;;;;;Top;
IC3;1;Accelerometers Triaxial low-g 12bit Acceleration Sensor;BMA423_BMA423;BMA423;;;;;Top;
IC9;1;Buck-Boost Regulator Positive Output Step-Up/Step-Down I2C DC-DC Controller IC 15-WL-CSP (BSC) (1.4x2.3);RT6160AWSC_BGA15C40P3X5_140X230X60;RT6160AWSC;;;;;Top;
J1;1;FFC & FPC Connectors 0.5mm FPC RA SMT Dual Contact 24Ckt;503480-2400_5034802400;503480-2400;;;;;Top;
J2;1;CABLE ADAPTER 6 POS;TC2030-IDC_TC2030IDC;TC2030-IDC;;;;;Top;
J4;1;Check availability;KINGHELM_KH-TYPE-C-16P;KH-TYPE-C-16P;;;;;Top;
L1;1;Generic chip inductor;NORDIC_NRF_2_RESC0402_L;3.9nH;;;;;Top;
L2;1;Generic chip inductor;NORDIC_NRF_2_RESC0402_L;10µH;;;;;Top;
L3;1;Generic chip inductor;NORDIC_NRF_2_RESC0402_L;15nH;;;;;Top;
L5;1;;ESP32_C6_LIBRARY_2_IND_4828-WE-TPC_WRE;68uH;;;;;Top;
L7;1;SMD / SMT Inductors (Coils), L=0.47?H, L x W x T :;MLP2016SR47MT0S1_INDC2016X100N;MLP2016SR47MT0S1;;;;;Top;
Q1;1;P-channel MOSFETs;ESP32_WROVER_SPARKFUN-DISCRETESEMI_SOT23-3;20V/4.2A/52mΩ/1.4W;;;;;Top;
Q3;1;MOSFET N-Ch 30V 1.5A TrenchFET SC70 Vishay Si1308EDL-T1-GE3 N-channel MOSFET Transistor, 1.5 A, 30 V, 3-Pin SC-70;SOT65P210X110-3N;SI1308EDL-T1-GE3;;;;;Top;
R_PWR_EPD, R2_EP_DR, R7, R8;4;7.68k 0201 Thin Film Surface Mount Fixed Resistor +/-0.5% 0.031W CPF0201D7K68C1;CPF0201D7K68C1_0201;10K;;;;;Top;
R_TYPE_SEL;1;7.68k 0201 Thin Film Surface Mount Fixed Resistor +/-0.5% 0.031W CPF0201D7K68C1;CPF0201D7K68C1_0201;2.2;;;;;Top;
R1_EP_DR;1;7.68k 0201 Thin Film Surface Mount Fixed Resistor +/-0.5% 0.031W CPF0201D7K68C1;CPF0201D7K68C1_0201;0.47;;;;;Top;
R1_USB, R2_USB;2;7.68k 0201 Thin Film Surface Mount Fixed Resistor +/-0.5% 0.031W CPF0201D7K68C1;CPF0201D7K68C1_0201;5K1;;;;;Top;
R2, R4;2;7.68k 0201 Thin Film Surface Mount Fixed Resistor +/-0.5% 0.031W CPF0201D7K68C1;R0201;0;;;;;Top;
R3;1;7.68k 0201 Thin Film Surface Mount Fixed Resistor +/-0.5% 0.031W CPF0201D7K68C1;CPF0201D7K68C1_0201;0;;;;;Top;
R5;1;7.68k 0201 Thin Film Surface Mount Fixed Resistor +/-0.5% 0.031W CPF0201D7K68C1;CPF0201D7K68C1_0201;10k;;;;;Top;
R9;1;7.68k 0201 Thin Film Surface Mount Fixed Resistor +/-0.5% 0.031W CPF0201D7K68C1;R0201;10k;;;;;Top;
R17, R18;2;7.68k 0201 Thin Film Surface Mount Fixed Resistor +/-0.5% 0.031W CPF0201D7K68C1;R0201;3K3;;;;;Top;
SJ1;1;SMD solder JUMPER;JUMPER_SJ;;;;;;Top;
SW_DN, SW_ENT, SW_UP;3;;SW_EVP-AKE31A_PAN;2025-10-22_07-23-44_LIBRARY_EVP-AKE31ASW_EVP-AKE31A_PAN;;;;;Top;
TP_3.3V, TP_3V3, TP_BAT_GND, TP_GND, TP_ON, TP_OP, TP_RESET, TP_SCL, TP_SDA, TP_SWDCLK, TP_SWDIO, TP_SWO, TP_VBAT, TP_VREG;14;Test pad;HECTOR_WATCH_1_TP20R;HECTOR_WATCH_1_TPTP20R;;;;;Top;
U1;1;nRF52840;NORDIC_NRF_4_AQFN50P700X700X85_HS-74N;NRF52840_QF;;;;;Top;
U3;1;Check availability;SON50P200X200X80-9N;MAX17048G+T10;;;;;Top;
X1;1;;NORDIC_NRF_BT-XTAL_2016_N;32MHz;;;;;Top;
X2;1;;NORDIC_NRF_1_XTAL_3215_N;32.768kHz;;;;;Top;

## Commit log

2026-04-10 Create LICENSE
2026-04-20 Rename Top_layer.png to Top_Layer.png
2026-04-21 Fisier nou .step

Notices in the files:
parts and their libraries:
COPYRIGHT: Copyright (C) 2024 Ultra Librarian. All rights reserved.
COPYRIGHT: Copyright (C) 2025 Ultra Librarian. All rights reserved.
